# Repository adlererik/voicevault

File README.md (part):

# VoiceVault

**A dedicated encrypted voice device, being developed and tested in software before hardware is built.**

A phone can be an excellent communications modem and an unsafe place to handle a private conversation. VoiceVault explores a different boundary: put the microphone path, audio codec, encryption keys, verified contacts and call approval inside a separate device. Give the phone encrypted media to forward.

The intended adversary has **NSA-class capabilities**: both phones may already be completely compromised through Pegasus-like spyware, zero-day or zero-click exploits, and telecommunications and relays may be controlled by the attacker. **Supply-chain attacks are excluded from the current threat model.** The project starts after phone compromise; it does not attempt to prevent or reproduce the exploit that compromised the phone.

**Today:** working Rust voice simulations, hostile-phone processes, lifecycle security models, a live device-and-test dashboard and a linked Cortex-M33 diagnostic. **Destination:** a small independent voice endpoint with its own trusted display, wired headset audio, replaceable battery, wired charging and a carefully isolated BLE connection to a phone. No physical VoiceVault device has been built.

[Project vision](docs/PROJECT_VISION.md) · [Architecture](docs/ARCHITECTURE.md) · [Threat model](docs/THREAT_MODEL.md) · [Every security control](docs/SECURITY_CONTROLS.md) · [Why these algorithms](docs/CRYPTOGRAPHY.md) · [Test evidence](docs/RESULTS.md) · [Hardware roadmap](docs/ROADMAP.md) · [Hybrid call security](docs/POST_QUANTUM.md)

## Start here: using the two labs

**[Read the beginner's guide to `lab` and `firmware-lab`](docs/LABS_GUIDE.md)** for step-by-step instructions, screen controls, listening, test results, saved files and troubleshooting.

| I want to… | Use |
|---|---|
| Watch software voice calls through hostile phone processes | `./lab demo --seconds 30` at <http://127.0.0.1:8765/> |
| Run the full eleven-group native verification suite | `./lab watch` |
| Use the ARM device screen on the configured local workstation | `./firmware-lab device` at <http://127.0.0.1:8765/firmware> |
| Understand every option before starting anything | `./lab --help`, or local `./firmware-lab --help`; add `COMMAND --help` for details |

The labs reuse trusted Rust building blocks and test different surroundings. They have separate verdicts; neither automatically qualifies the other or a physical board. **The firmware runtime is currently local development work, not a runnable package in this GitHub checkout.** The guide explains that availability boundary and its public-test-key, timing and hardware limits.

[Native command reference](docs/CLI_REFERENCE.md) · [Local firmware command reference](hardware/firmware-lab/CLI.md) · [Native tool setup](docs/DEVELOPMENT.md)

## Hardware laboratory

**The [VoiceVault C1 LQFP144 layout](hardware/rev-c1/README.md) reached 98% routing.** Quilter finished six candidates at **21:19 CET on 16 November**. Independent KiCad review of candidate 3.1 confirms **six unfinished connections, zero copper shorts and zero schematic mismatches**. Hole-clearance, antenna and placement findings remain; no board is accepted for manufacture. [Actual returned PCB views and native findings](hardware/evidence/2026-11-17/c1-return-review/README.md). The owner subsequently authorized local KiCad repairs in a [separate checkpoint](hardware/rev-c1/local-repair-01/README.md). The uploaded input and raw cloud result remain preserved; [repair evidence](hardware/evidence/2026-11-17/c1-local-repair/README.md) tracks the additional wiring required by power-layout corrections.

The [latest checked local repair](hardware/rev-c1/local-repair-03/README.md) has 17 remaining native opens, zero KiCad rule violations and zero schematic mismatches. All three converter inductors are on their controllers’ faces; their switching connections have no vias, including the 2.924 mm MCU connection. Routing is still in progress. [Front and back CAD renders](hardware/visuals/2026-11-17/README.md) use the actual layout with some approximate component bodies.

C1 uses **STM32U5G9ZJT6Q LQFP144**, retaining the STM32U5G9ZJ platform while moving the MCU connections to accessible perimeter leads. The [package evaluation](hardware/rev-c/LQFP_EVALUATION.md) led to a complete 144-pin remap, a corrected hardware microSD clock on **PB13**, and three additional supply bypass capacitors. It retains **one NXP SE050E2 secure element, QFN nRF52832 BLE, a replaceable protected BL-5C-style lithium-ion pack interface, wired charging, trusted display/touch, wired audio, physical mic disconnect, offline microSD and separate development debug connectors**. Qi, NFC and vibration remain removed.

There are **199 electrical components—97 fewer than B0—plus 13 probes and four mounting holes: 216 footprints**. The provisional rectangle remains 70 × 45 mm, with a six-layer stack and ordinary vias. Populated-board fit, final routing and hardware qualification remain unverified.

**Checked input:** KiCad 10.0.8 reports **zero ERC violations and zero schematic-to-PCB mismatches**. All 144 MCU pins, 55 signal functions, 711 functional pin-net assignments and 72 retained critical circuit checks pass. Seven corrupted-pin controls and five isolated RF rule controls pass. The empty input has **587 connections to route**; that is intentionally a fresh layout, not a repaired-board result. All 18 server input files exactly match the checked source, and downloaded cloud settings match 76 reviewed bypass entries, 14 current budgets, three converter loops, four crystals and 21 proximity requirements. [Actual checks, hashes and limits](hardware/evidence/2026-11-16/c1-preparation/README.md).

*Native KiCad view of candidate 3.1, showing the central LQFP144 MCU. This reviewed cloud return has remaining failures and has not replaced the live board.*

**ngspice 47** completed 27 revised passive MCU core-output sensitivity cases. The model has no MCU regulator control loop and does not qualify stability or hardware behavior. Earlier unchanged C0 subcircuit studies include 772 passive audio/backlight cases, 16 secure-bus RC cases and a supplier radio-switch model; the main buck-boost supplier model remains numerically blocked. [C1 evidence](hardware/evidence/2026-11-16/c1-preparation/README.md) · [Earlier subcircuit reports and plot](hardware/evidence/2026-11-16/quilter-launch/README.md).

**Manufacturing remains blocked.** Final routing/connectivity, native DRC, RF/power/audio/mechanical review, battery/holder and assembly sourcing, production firmware and real hardware security tests remain open. No board has been ordered or built, and no purchase or paid service was used.

The [original BGA C0 revision](hardware/rev-c/README.md), rejected [95% Quilter return](hardware/evidence/2026-11-16/quilter-retry-01-return/README.md), [isolated 62-open repair](hardware/rev-c/local-repair-01/README.md), live B0 and all earlier FreeRouting/cloud evidence remain preserved. [Historical hardware laboratory and tool/MCP details](hardware/README.md).

## The idea: move the endpoint

An ordinary encrypted calling app processes plaintext on the phone. Once an attacker controls that operating system, network encryption alone cannot protect audio the operating system can already access.

VoiceVault's intended device owns the sensitive endpoint. Contacts are verified there, calls are approved there, and audio is encoded and encrypted there before reaching the phone. The phone carries encrypted records and necessary signaling; it does not become a trusted authority for identities, consent, keys, time, entropy or firmware.

This distinction depends on the physical audio path. The proposed host-phone arrangement includes removing its microphones and speakers, keeping voice on an external wired headset connected to VoiceVault, and validating remaining acoustic pickup paths. An unmodified compromised phone nearby can still record speech through its own microphone. [Why a separate device, and its limits](docs/DEVICE_RATIONALE.md)

*Architecture illustration. Analog audio and BLE are hardware targets; current calls use synthetic audio and bounded local IPC. Public signaling and transport metadata remain observable.*

## A real software foundation

The lab makes two endpoints conduct a simultaneous encrypted voice exchange through two hostile phone processes and a relay. It uses actual Opus and actual cryptography, produces recovered WAV files, injects delivery faults, and records results for inspection.

| Built and exercised | What it establishes |
|---|---|
| Two voice endpoints and three hostile transport processes | A concrete separation between trusted audio/key handling and untrusted delivery, under a trusted Linux host |
| Confirmed enrollment, pinned contacts and signed invitations | Explicit identity, consent, replay and accepted-call binding rules |
| Real Opus → Noise encryption → hostile transport → authentication → decode | An executable media pipeline, including loss and malformed-input handling |
| Stored-contact, entropy, radio and offline-update models | Testable device-local policy before selecting physical chips |
| The same trusted crates compiled without `std` and linked for Cortex-M33 | Functional CPU execution and measured memory fit under a named capacity budget |
| An event-backed dashboard with searchable individual results | Visible checks, named test outcomes, attack traces and saved replays |

A tested model is not a finished hardware protection. The [assurance case](docs/ASSURANCE.md) states which assumptions each result depends on.

## The threat model and the protections

The attacker may observe, drop, replay, modify, reorder, delay and inject traffic; collude across both phones and relays; impersonate contacts; flood ingress; and try to turn malformed messages into unauthorized device actions. The design also tests a malicious authenticated peer, because having a valid key does not make compressed audio harmless.

| Attack or failure | Protection in the software model | Boundary |
|---|---|---|
| Intercept or modify voice | ChaCha20-Poly1305 under authenticated Noise transport keys | Trusted endpoints and sound implementations are assumed |
| Substitute a peer during enrollment | Noise XX, signed identity/DH records, full transcript comparison and confirmation on both sides | Trusted local comparison is required; hardware UI is future work |
| Spoof a contact or call invitation | Pinned Ed25519 identity, recipient binding, boot challenge, expiry and persisted counters | Invitation metadata itself is not confidential |
| Reuse a different invitation for an authenticated call | The hybrid Noise prologue binds the signed offer and acceptance and both verified identities | Local approval remains separate from remote signaling |
| Save encrypted calls for future quantum decryption | Fresh X25519 and ML-KEM-768 establish each call, with the hybrid suite required | Depends on the hybrid construction, trusted endpoints and erasure |
| Replay media or poison the replay window | Monotonic sending, directional keys, authenticated counter/slot checks and a bounded replay bitmap | Invalid input cannot commit incoming replay state |
| Activate audio through the phone | Local consent plus encrypted Confirm/Ready; no radio mic/consent opcode | Actual headset and physical disconnect still need validation |
| Infer speech or silence from record length | CBR Opus, DTX off, fixed 128-byte records and encrypted filler | Call boundaries, timing errors, location and correlation remain visible |
| Exhaust queues or force a burst after a stall | Bounded ingress, assembly and jitter queues; expiry; absolute deadlines; missed slots discarded | A hostile network can still deny service |
| Roll back stored contacts or signaling counters | Owner-bound AEAD snapshots tied to a protected monotonic generation | Protected storage is modeled, not a chip driver |
| Push firmware through the phone | No remote updater; locally authorized signed-image policy | Physical boot/update enforcement remains future hardware work |
| Install an old, corrupt or wrong-device image | Target/version/hash/signature checks, protected floor, two banks and readback | Real flash and counter atomicity are unmeasured |
| Interrupt an offline update | Preserve the active bank, write header last, verify before boot/version handoff | Tests cover modeled write cuts and selected torn writes |
| Weaken randomness through the phone | Onboard-only entropy-source interface, failure checks and two-source policy | Hardware entropy quality and independence need measurement |
| Keep using a closed or expired session | Irreversible close, owned key destruction, bounded media epoch and fresh handshake | Complete erasure and seamless renewal remain open |

The [complete control register](docs/SECURITY_CONTROLS.md) links each protection to its code, evidence, assumptions and remaining hardware work.

## Why these cryptographic choices?

| Choice | Role and reason |
|---|---|
| **X25519** | Compact Diffie–Hellman key exchange with fresh per-call ephemeral secrets; separate from signing identities |
| **ML-KEM-768** | Adds a fresh post-quantum secret for each call using the portable `libcrux-ml-kem` implementation |
| **Ed25519** | Signed identities, contact bindings, invitations and offline-image authorization |
| **ChaCha20-Poly1305** | Established authenticated encryption for voice and stored snapshots; suitable for portable software implementations |
| **BLAKE2s** | A 32-bit-oriented hash for the selected Noise suite, domain-separated bindings and firmware digests |
| **Noise's HMAC/HKDF-BLAKE2s** | An established transcript-bound key schedule and separate transport keys for each direction |
| **Noise XX / KKhfs through Snow** | XX for first enrollment and the experimental hybrid KK modifier for calls between pinned contacts |
| **Opus** | Practical speech compression; hard CBR and no DTX work with the outer fixed-size envelope |
| **Rust with `no_std` integration** | Safe parsing/state code and bounded interfaces that can migrate toward embedded firmware |

The hybrid suite is required for new calls. Both peers authenticate the full exchange and its algorithm suite before local consent and encrypted confirmation open audio. ML-KEM-768 is an explicit exception to the owner’s preference to avoid NIST algorithms where practical. [Protocol and wire format](docs/POST_QUANTUM.md) · [Cryptographic rationale](docs/CRYPTOGRAPHY.md)

## Evidence you can inspect

The hybrid v2 run on **2026-11-11** passed **all 11 required groups and 48 checks**. The suite recorded 68 named outcomes, including five bounded Kani checks, and ran eight fuzz campaigns for at least 120 seconds each. It also checked 80 ML-KEM-768 vectors. The altered-startup scenario verifies that a compromised phone cannot open either audio path by modifying the key exchange.

| Recorded result | Observation |
|---|---|
| Real encrypted audio | Both directions recovered generated audio through two hostile phone processes and a relay |
| Cortex-M33 execution | Hybrid startup, fragmentation and 32 Opus frames executed in QEMU |
| Linked image and observed stack | 863,104 bytes of a 983,040-byte slot and 84,876 bytes of a 131,072-byte stack reserve |
| Reference memory budget | 37,500 bytes unassigned after static state and stack/display/driver reservations |

[Latest raw results](docs/evidence/hybrid-v2/) · [What each fuzz target tests](docs/FUZZING.md) · [All recorded runs](docs/RESULTS.md) · [Embedded fit](docs/PLATFORM.md)

*Actual dashboard capture during hybrid handshake fuzzing. The device panels show the earlier live call in the same run. [Live call capture](docs/screenshots/command-deck-live-laptop.png) · [Historical full-suite completion](docs/screenshots/voicevault-complete.png)*

## See what is happening as it happens

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
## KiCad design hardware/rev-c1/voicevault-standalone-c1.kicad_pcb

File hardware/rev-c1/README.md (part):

# VoiceVault C1 — LQFP144 prototype

**Local repair is now authorized and in progress.** See the [latest checked repair: 17 opens, zero native violations](local-repair-03/README.md), the [preserved earlier repair](local-repair-01/README.md) and [native repair evidence](../evidence/2026-11-17/c1-local-repair/README.md). The six-open count below describes the untouched cloud return. Moving power parts and removing invalid copper required additional connections to be rebuilt in the repair copy.

**Quilter finished at 21:19 CET on 16 November 2026: six candidates, all reporting 98% routing. Not for fabrication.** Independent KiCad review of candidate 3.1 confirms **six missing connections, zero copper shorts and zero schematic-parity mismatches**, but hole-clearance and antenna-rule failures remain. [Actual returned board views, exact findings and next work](../evidence/2026-11-17/c1-return-review/README.md). The owner approved **STM32U5G9ZJT6Q** on 16 November 2026. C1 is a separate revision; all earlier revisions and results remain preserved.

[Open the completed C1 job](https://app.quilter.ai/jobs/6afb49addfae511781423d99?candidate=3) · [Recorded launch and settings](../evidence/2026-11-16/c1-preparation/launch.json). Candidate 3.1 was downloaded and reviewed in separate work folders; it has not replaced the checked input or live board and is not accepted for release.

[KiCad project](voicevault-standalone-c1.kicad_pro) · [Root schematic](voicevault-standalone-c1.kicad_sch) · [Clean PCB input](voicevault-standalone-c1.kicad_pcb) · [Review inventory](BOM-REVIEW.csv) · [Exact circuit target](board-target.json) · [Checked evidence](../evidence/2026-11-16/c1-preparation/README.md) · [Package evaluation](../rev-c/LQFP_EVALUATION.md)

## Implemented circuit changes

| Area | C1 change |
|---|---|
| MCU | STM32U5G9ZJT6Q, LQFP144, 20 × 20 mm body, 0.50 mm pitch; native symbol and 144-pad footprint |
| Pin mapping | All 144 physical pins checked against pinned ST data, including all 55 connected signal functions and 91 connected supply/reference/signal pins |
| microSD | Move SD_SCK_MCU from PC0, which lacks SPI2_SCK, to unused PB13 / pin 70; retain PC1 MOSI, PC2 MISO and PC7 software chip select |
| Supplies | Map every LQFP supply/ground pin explicitly; retain both VDD11 pins and connect **both** VDD11DSI pins to MCU_VDD11 |
| New bypass parts | C113 at VDD pin 122, C114 at VDD pin 144, C115 at VDD11DSI pin 20; each 100 nF / 10 V |
| Debug | Retain STDC14 SWD/SWO/UART and reset on package-correct pins; development access remains open |
| CAD consistency | Preserve explicit single-pad no-connect net names for native parity. JP501 is a copper solder bridge excluded from purchasing BOM, with matching symbol/footprint attributes |
| Cloud settings | Replace all old MCU ball identifiers with LQFP pin numbers; 76 actual rail/reference bypass definitions. Exclude 12 oscillator, RF, reset, audio-filter and timing capacitors from the supply-bypass list |

Inventory is **199 electrical footprints, 13 probes and four mounting holes: 216 total**, versus C0's 213. The only changed existing component value is U1's order code. Every existing functional non-MCU connection and all four mounting-hole positions are preserved. New MCU wiring is a package remap plus the explicit SD-clock correction. [Delta checks](../evidence/2026-11-16/c1-preparation/circuit-delta.json).

The one SE050E2, larger QFN nRF52832, BQ24074 wired charger, replaceable protected lithium pack interface, audio codec/headset/mic disconnect, display/touch, microSD and local controls remain. Qi, NFC and haptics remain removed. Battery/holder/display assembly acceptance, charging safety and production-ready component sourcing remain open; this inventory is not an assembler-approved order file.

## Power-pin allocation

| LQFP supply | Pins | Local 100 nF assignments |
|---|---|---|
| VDD | 25, 41, 55, 69, 83, 89, 95, 109, 122, 144 | C7, C12, C17, C14, C10, C11, C9, C16, C113, C114 |
| VDDDSI | 13 | C8; C110 provides the existing additional bulk bypass |
| VDD11DSI | 14, 20 | C23, C115; connect to MCU_VDD11, never directly to 3.3 V |
| VDD11 | 67, 142 | C22, C24; C107/C27 retain the two 2.2 µF core capacitors |
| VDDSMPS | 65 | C26; C25/C108 retain existing input bulk capacitance |
| Other domains | VBAT 6, VREF+ 34, VDDA 35, VDDUSB 108, VDDIO2 131 | Existing domain-specific caps remapped and checked |

L1 remains between VLXSMPS pin 64 and MCU_VDD11. VSSSMPS pin 66 is ground. Correct values and pin associations are necessary; actual close placement, short switching loops, return paths, capacitor derating/ESR and measured regulation remain acceptance gates. The [full pin/net CSV](../evidence/2026-11-16/c1-preparation/mcu-pin-net.csv) includes unused and ground pins.

## Verification completed

Using KiCad **10.0.8**:

- Native ERC: **zero violations**.
- Native DRC of the off-board inventory: **zero layout violations**; explicit schematic-parity check: **zero mismatches**.
- Native netlist/PCB comparison: **711 functional pin-net assignments**, 826 exported nodes including explicit unused pins.
- All 144 MCU pin assignments, 55 signal functions and the retained 72 critical circuit/boundary checks pass. **Seven deliberately corrupted mappings are rejected**, including SD-clock, core/DSI power, debug, radio-to-secure-bus and C115 faults.
- **Five isolated native RF controls pass**: same-side feed allowed; opposite-side, inner-layer, wrong-net and out-of-corridor routes rejected. These fixtures do not route the real board.
- Full native ratsnest: **587 connections to route**. This is a new blank PCB, not the 62-open repaired BGA layout. There are **zero tracks, vias or copper pours**. All 212 non-mounting footprints are unlocked and parked outside the outline for Quilter to place.

With **ngspice 47**, 27 bounded passive core-output cases include the extra DSI bypass capacitor and sweep assumed inductance, bulk-cap derating and winding resistance. Observed idealized core extrema are **1.0148–1.1854 V**. The model has an ideal averaged source and **no MCU regulator control loop**: these are sensitivity results, not stability, power-integrity or hardware qualification. Six simulator-result checks ensure aborted/incomplete/non-finite outputs cannot be called successful. Unchanged C0 power/audio model limitations remain open.

Run `./hardware/check --rev-c1` for the native circuit/pin checks. [Evidence and additional test commands](../evidence/2026-11-16/c1-preparation/README.md).

## Placement and routing plan

Quilter performed the original full placement and routing. The original uploaded C1 input in this directory contains no FreeRouting copper, prior cloud copper or local electrical placement. The owner later authorized local repairs in the separate checkpoint linked above. The first outline remains a provisional **70 × 45 mm** rectangle. The 23.3 mm MCU courtyard bounding box fits the bare outline; populated-board fit must be established by placement and mechanical review. A larger serviceable rectangle remains an option if the actual layout requires it.

Use the standard JLCPCB **six-layer 4 mil preset**, S/GND/S/S/GND/S, **1.538 mm modeled thickness**, ordinary **0.45/0.20 mm vias**, and 0.50 mm board margin. This is a layout study against provisional published limits, not a manufacturing-stack approval or price quote. Two ground references are retained; a dedicated power plane is not required by this study. Real trace/pour current capacity and RF impedance still need review.

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
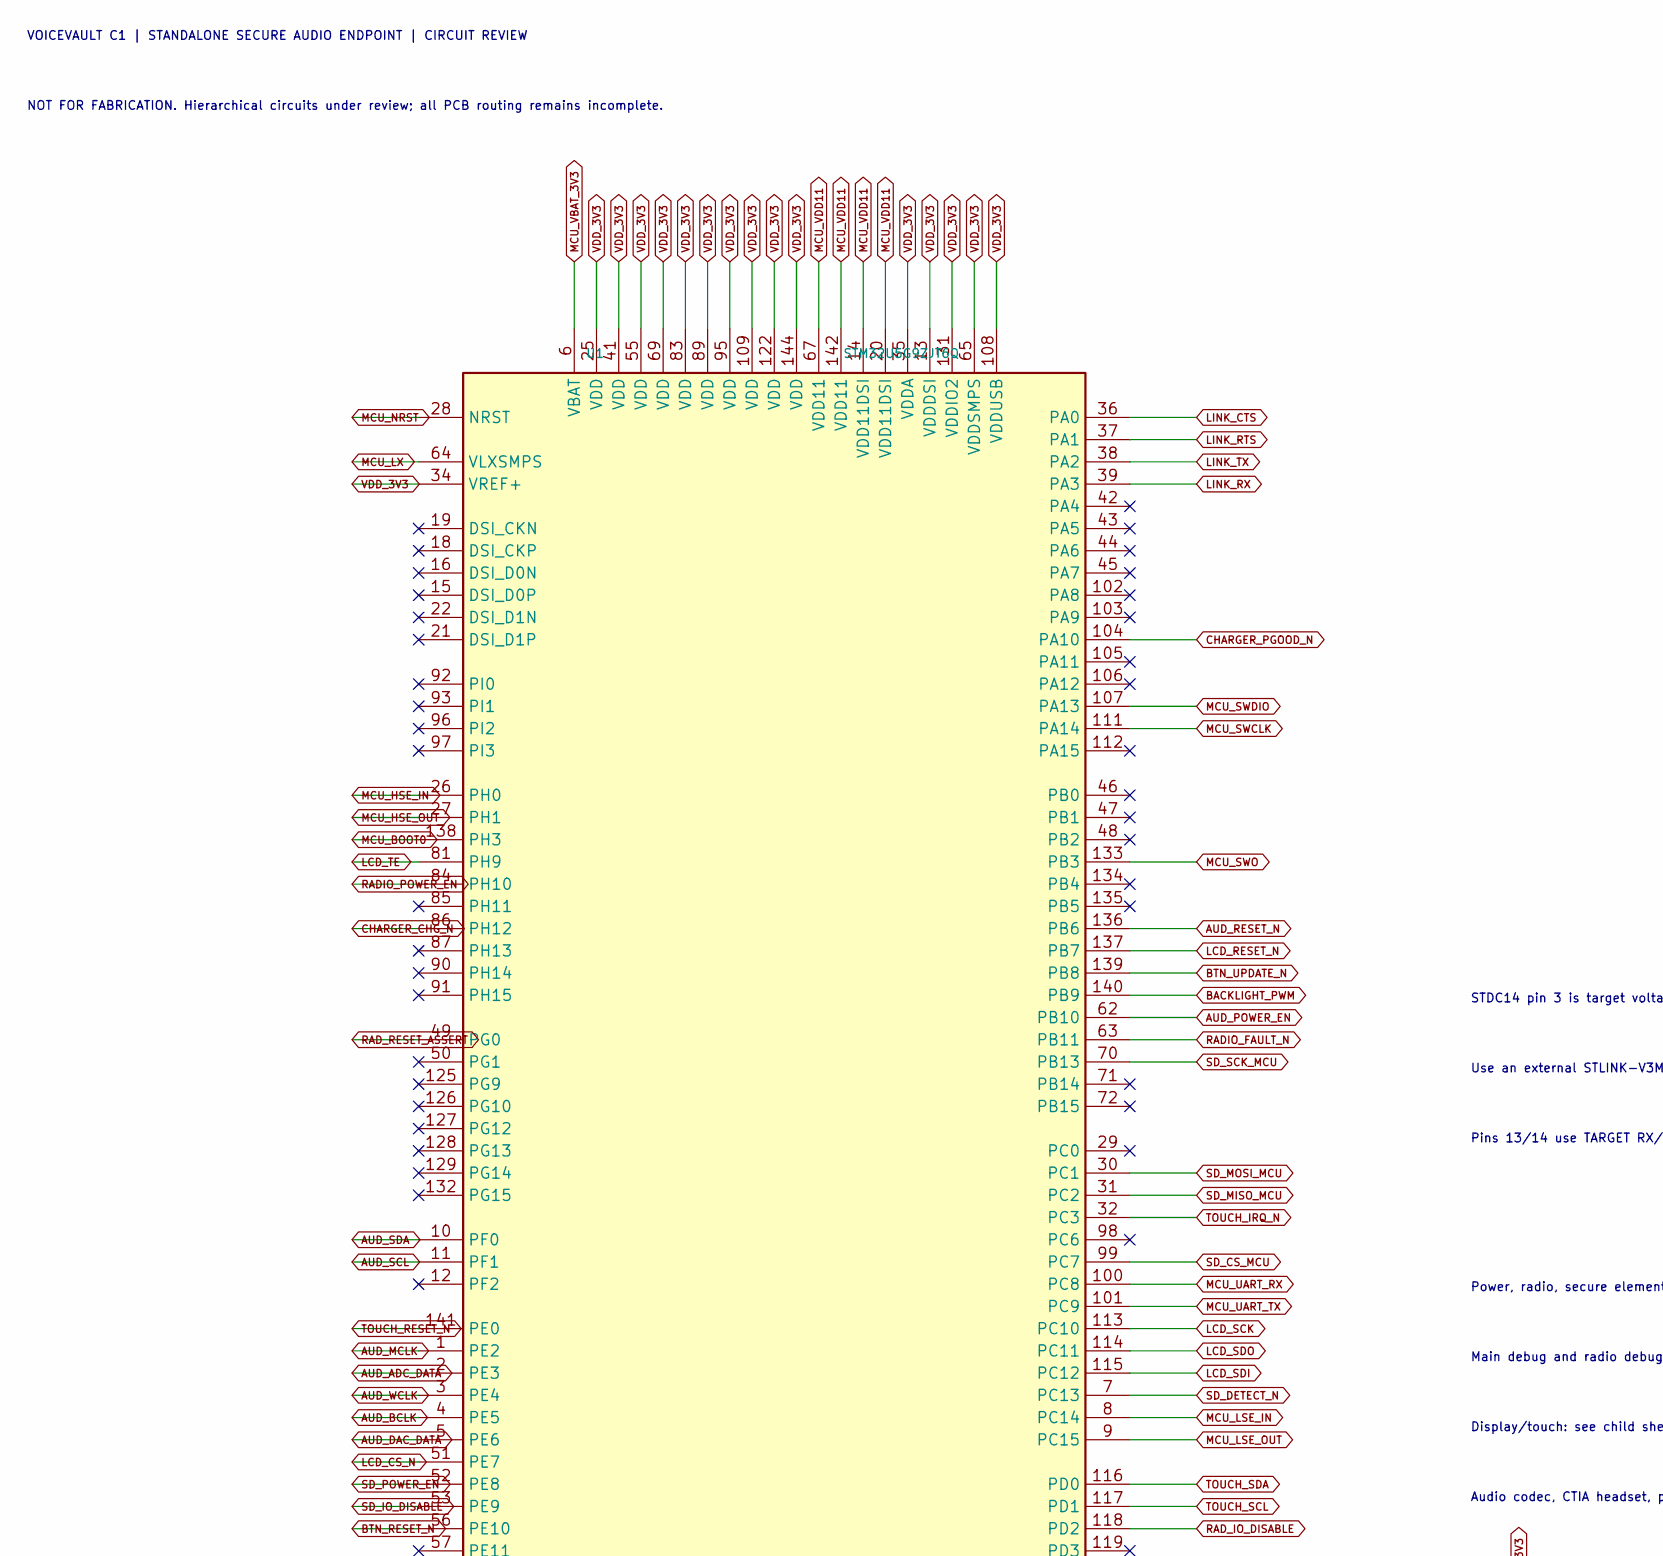
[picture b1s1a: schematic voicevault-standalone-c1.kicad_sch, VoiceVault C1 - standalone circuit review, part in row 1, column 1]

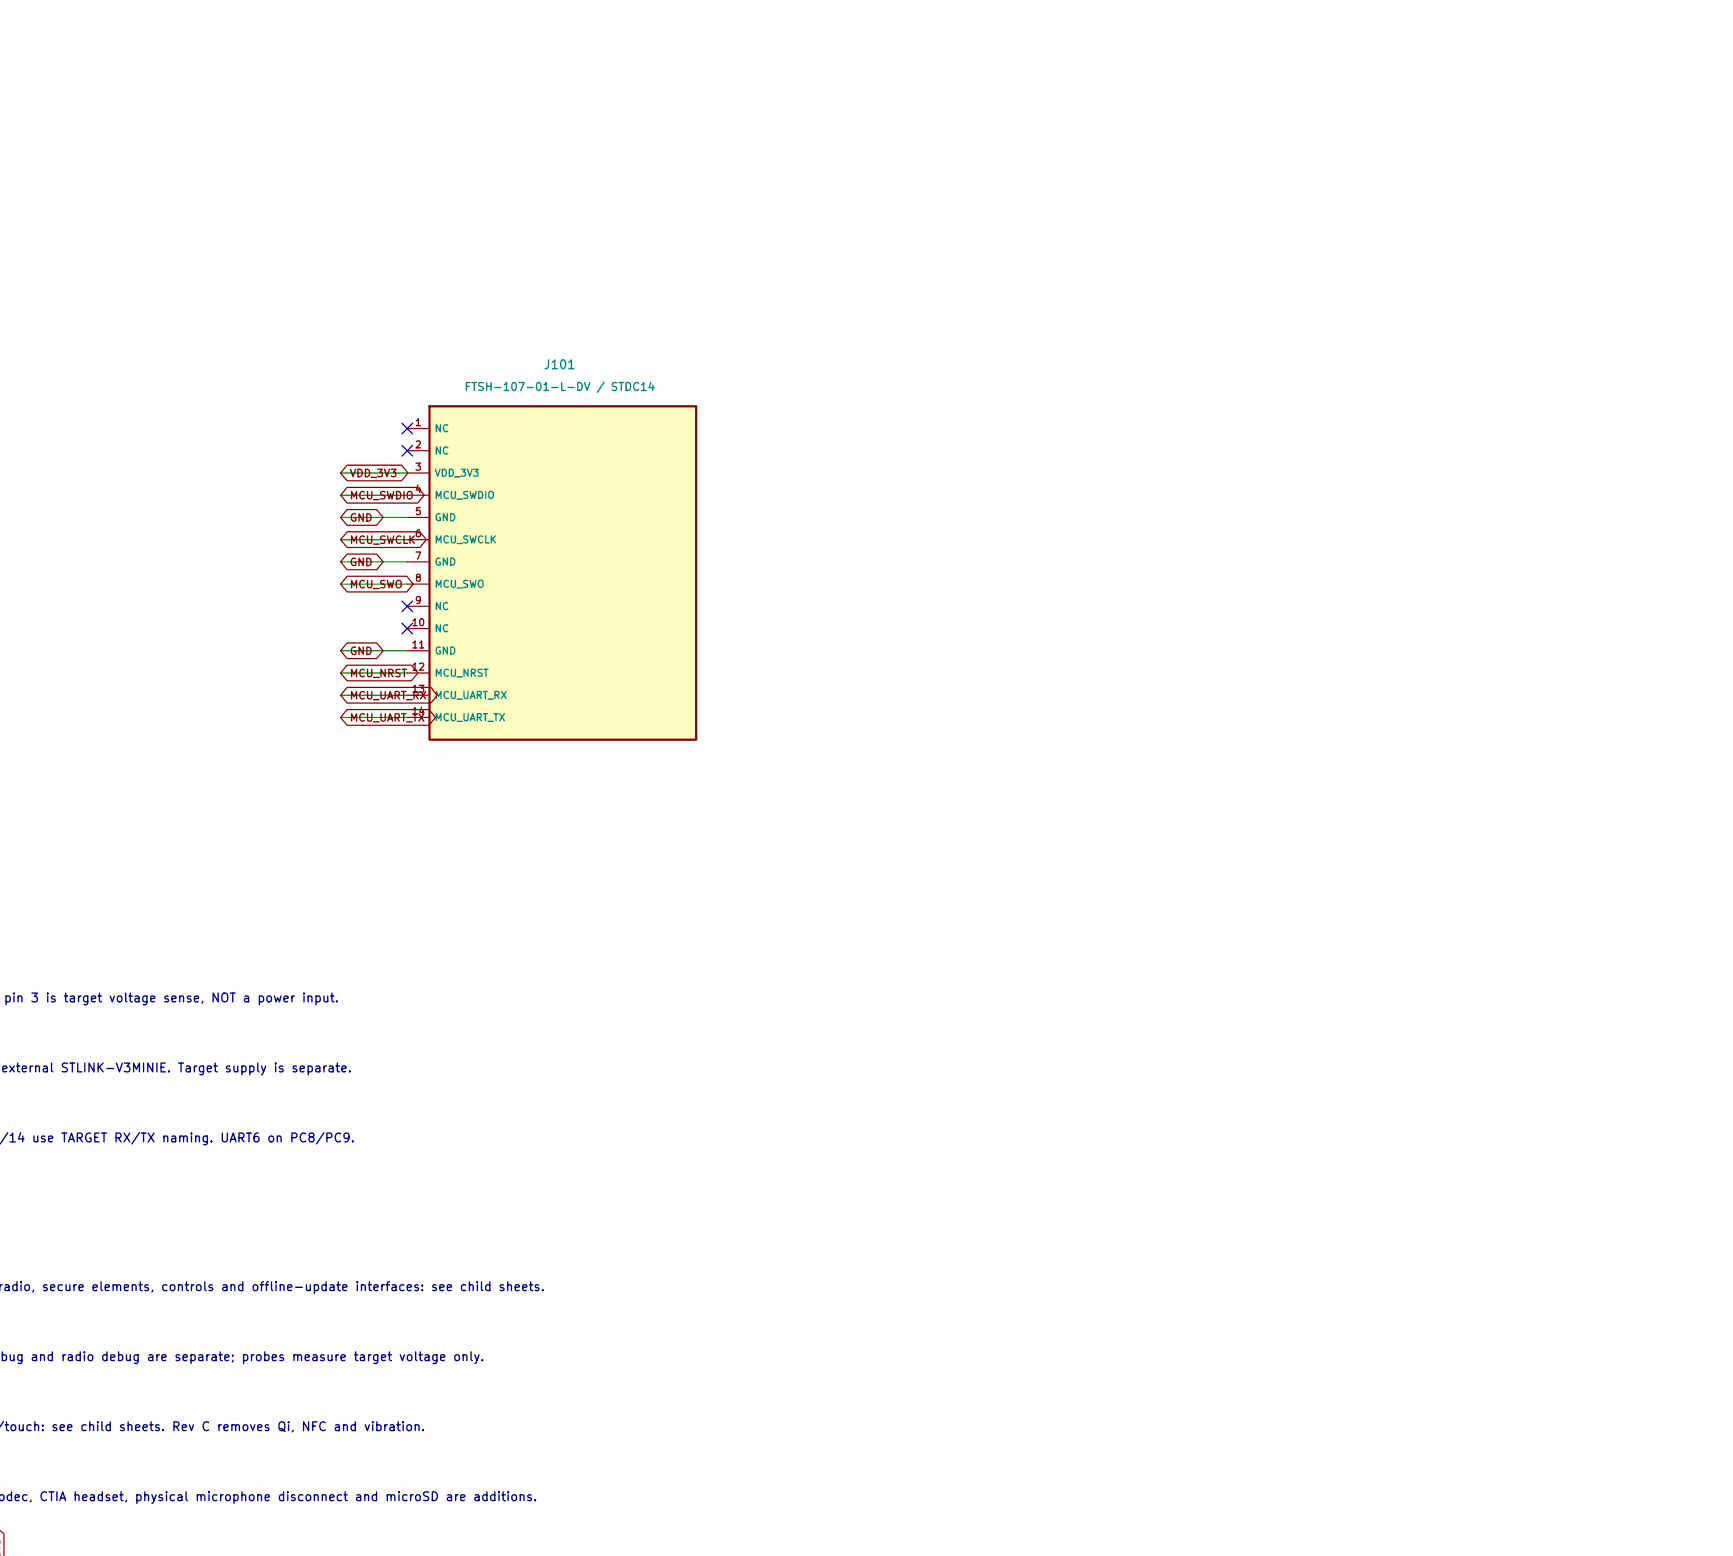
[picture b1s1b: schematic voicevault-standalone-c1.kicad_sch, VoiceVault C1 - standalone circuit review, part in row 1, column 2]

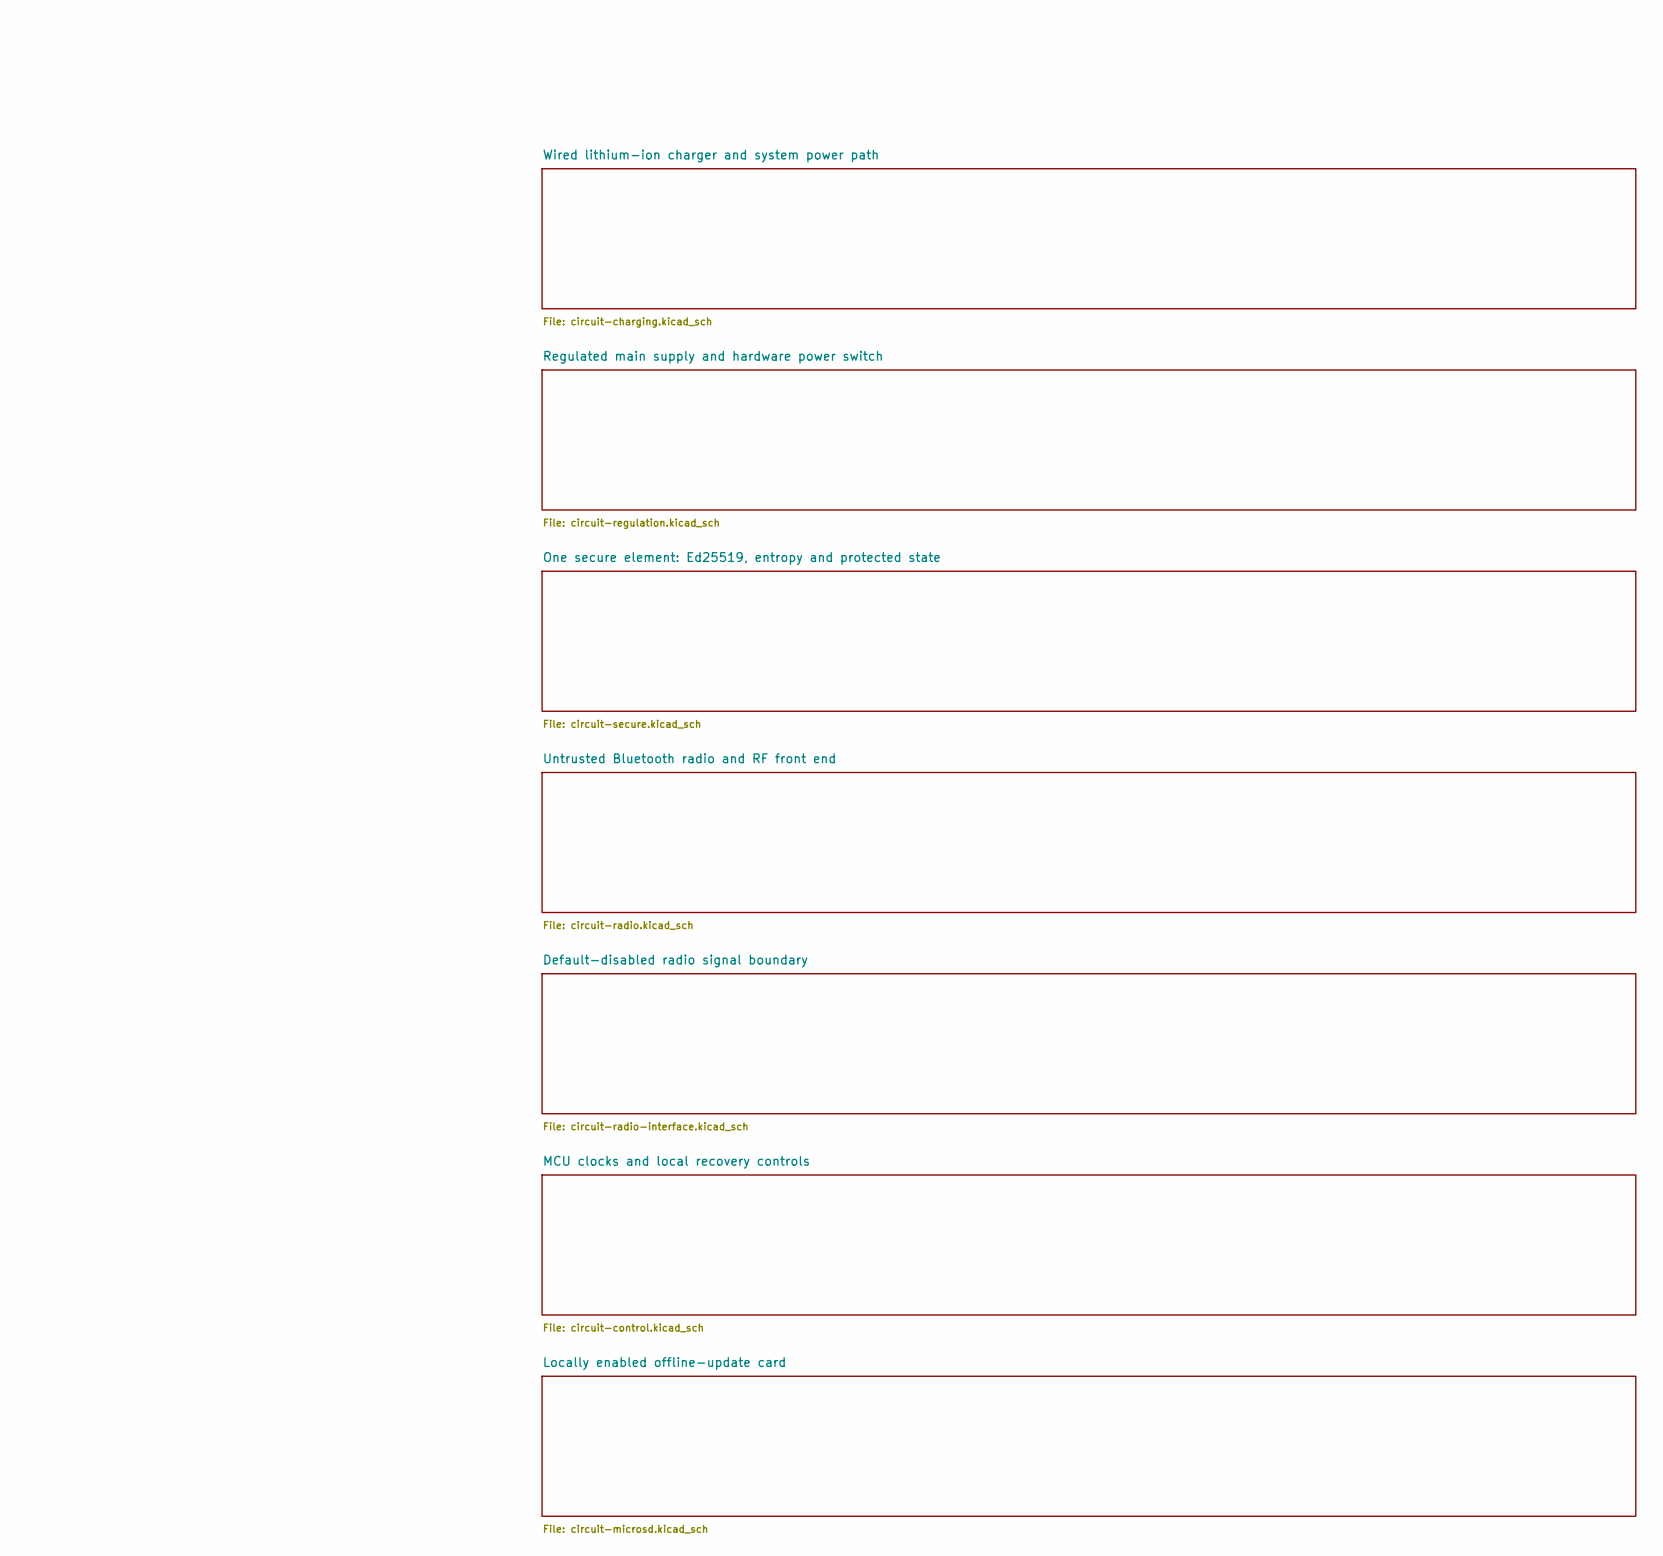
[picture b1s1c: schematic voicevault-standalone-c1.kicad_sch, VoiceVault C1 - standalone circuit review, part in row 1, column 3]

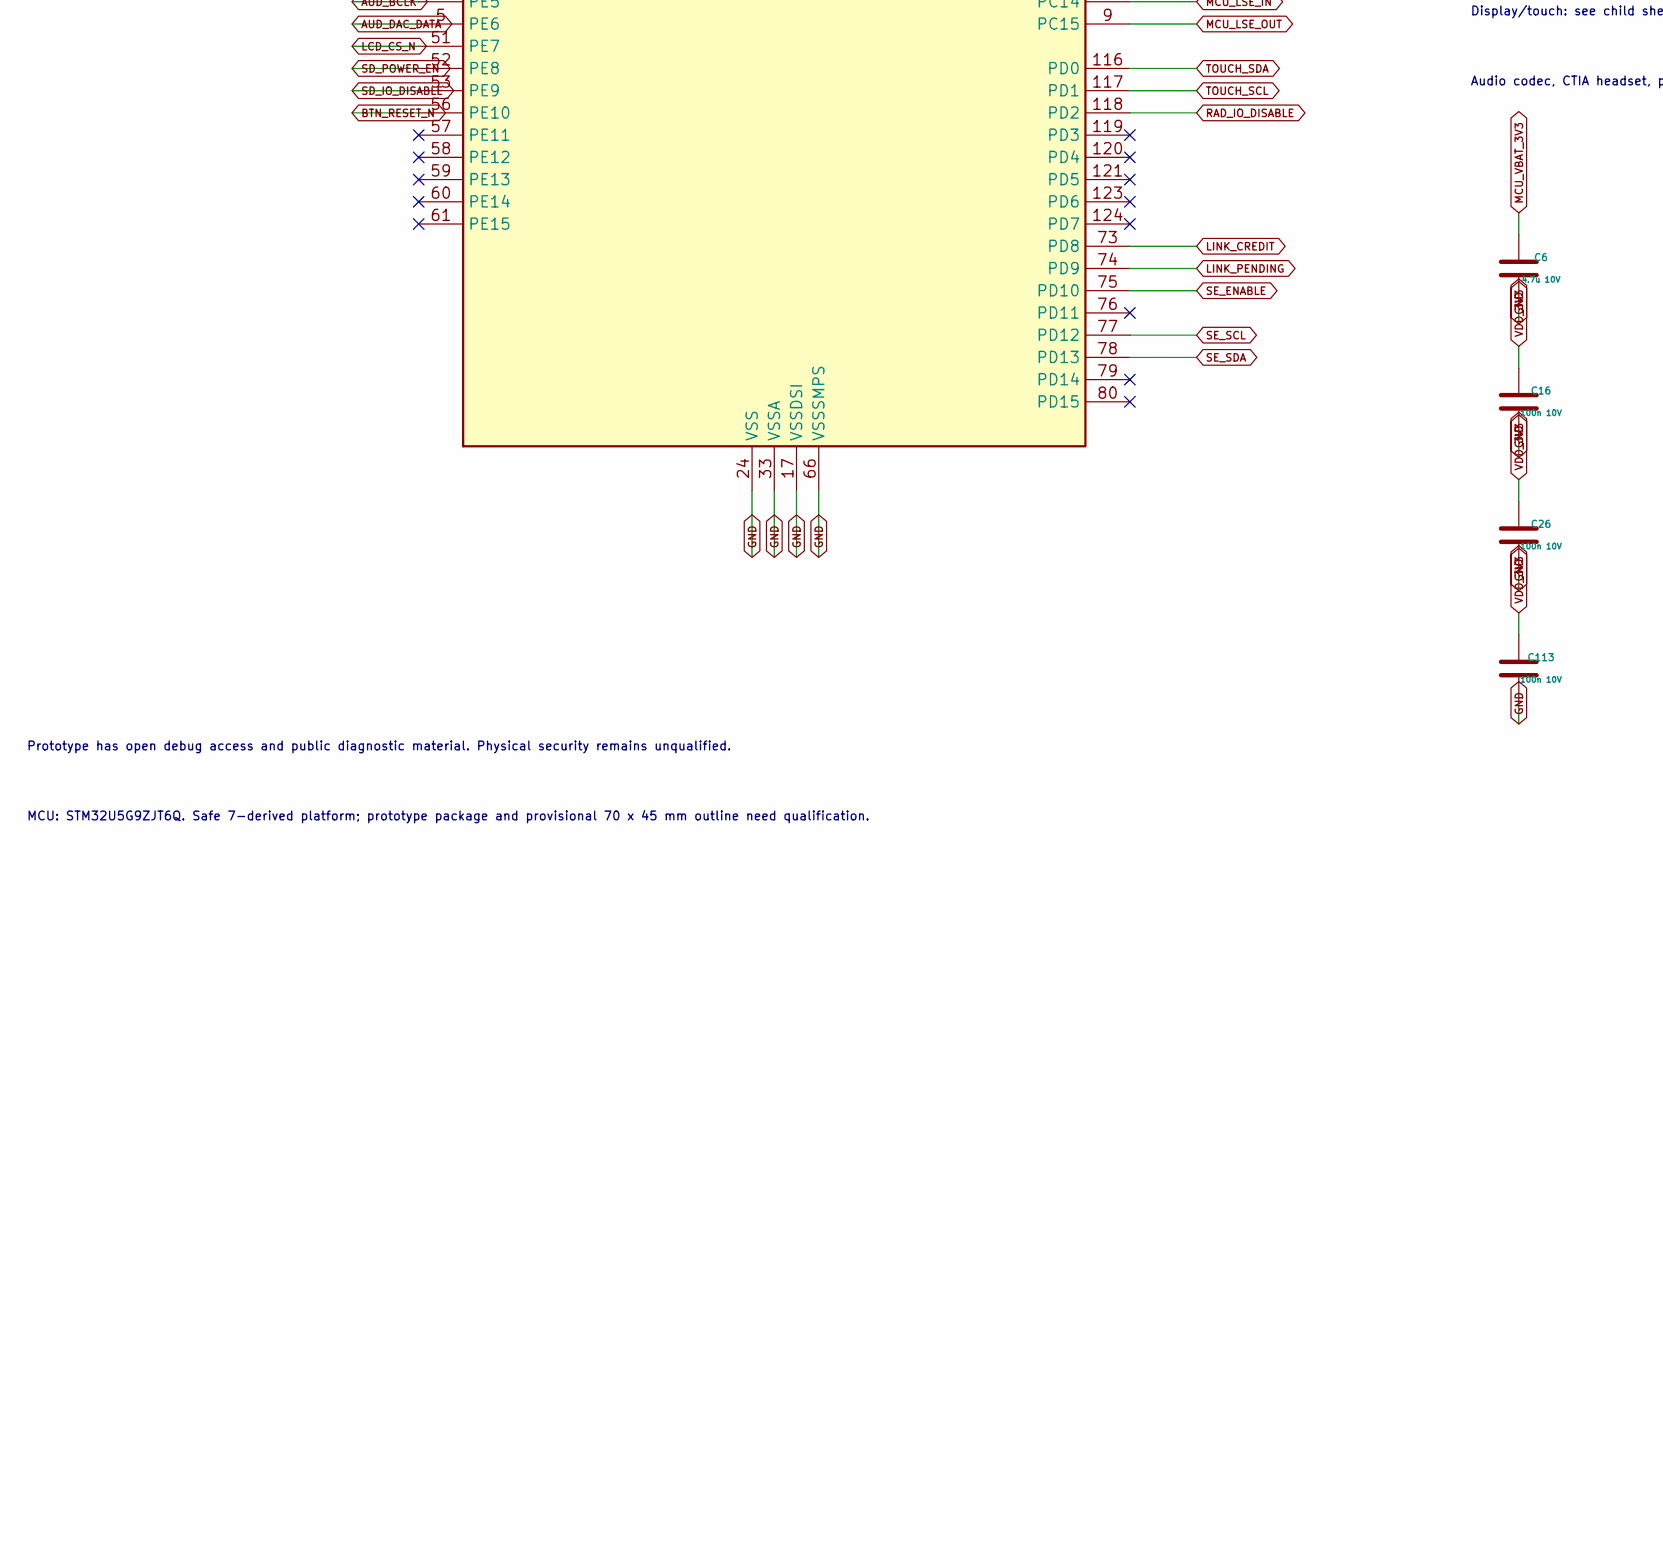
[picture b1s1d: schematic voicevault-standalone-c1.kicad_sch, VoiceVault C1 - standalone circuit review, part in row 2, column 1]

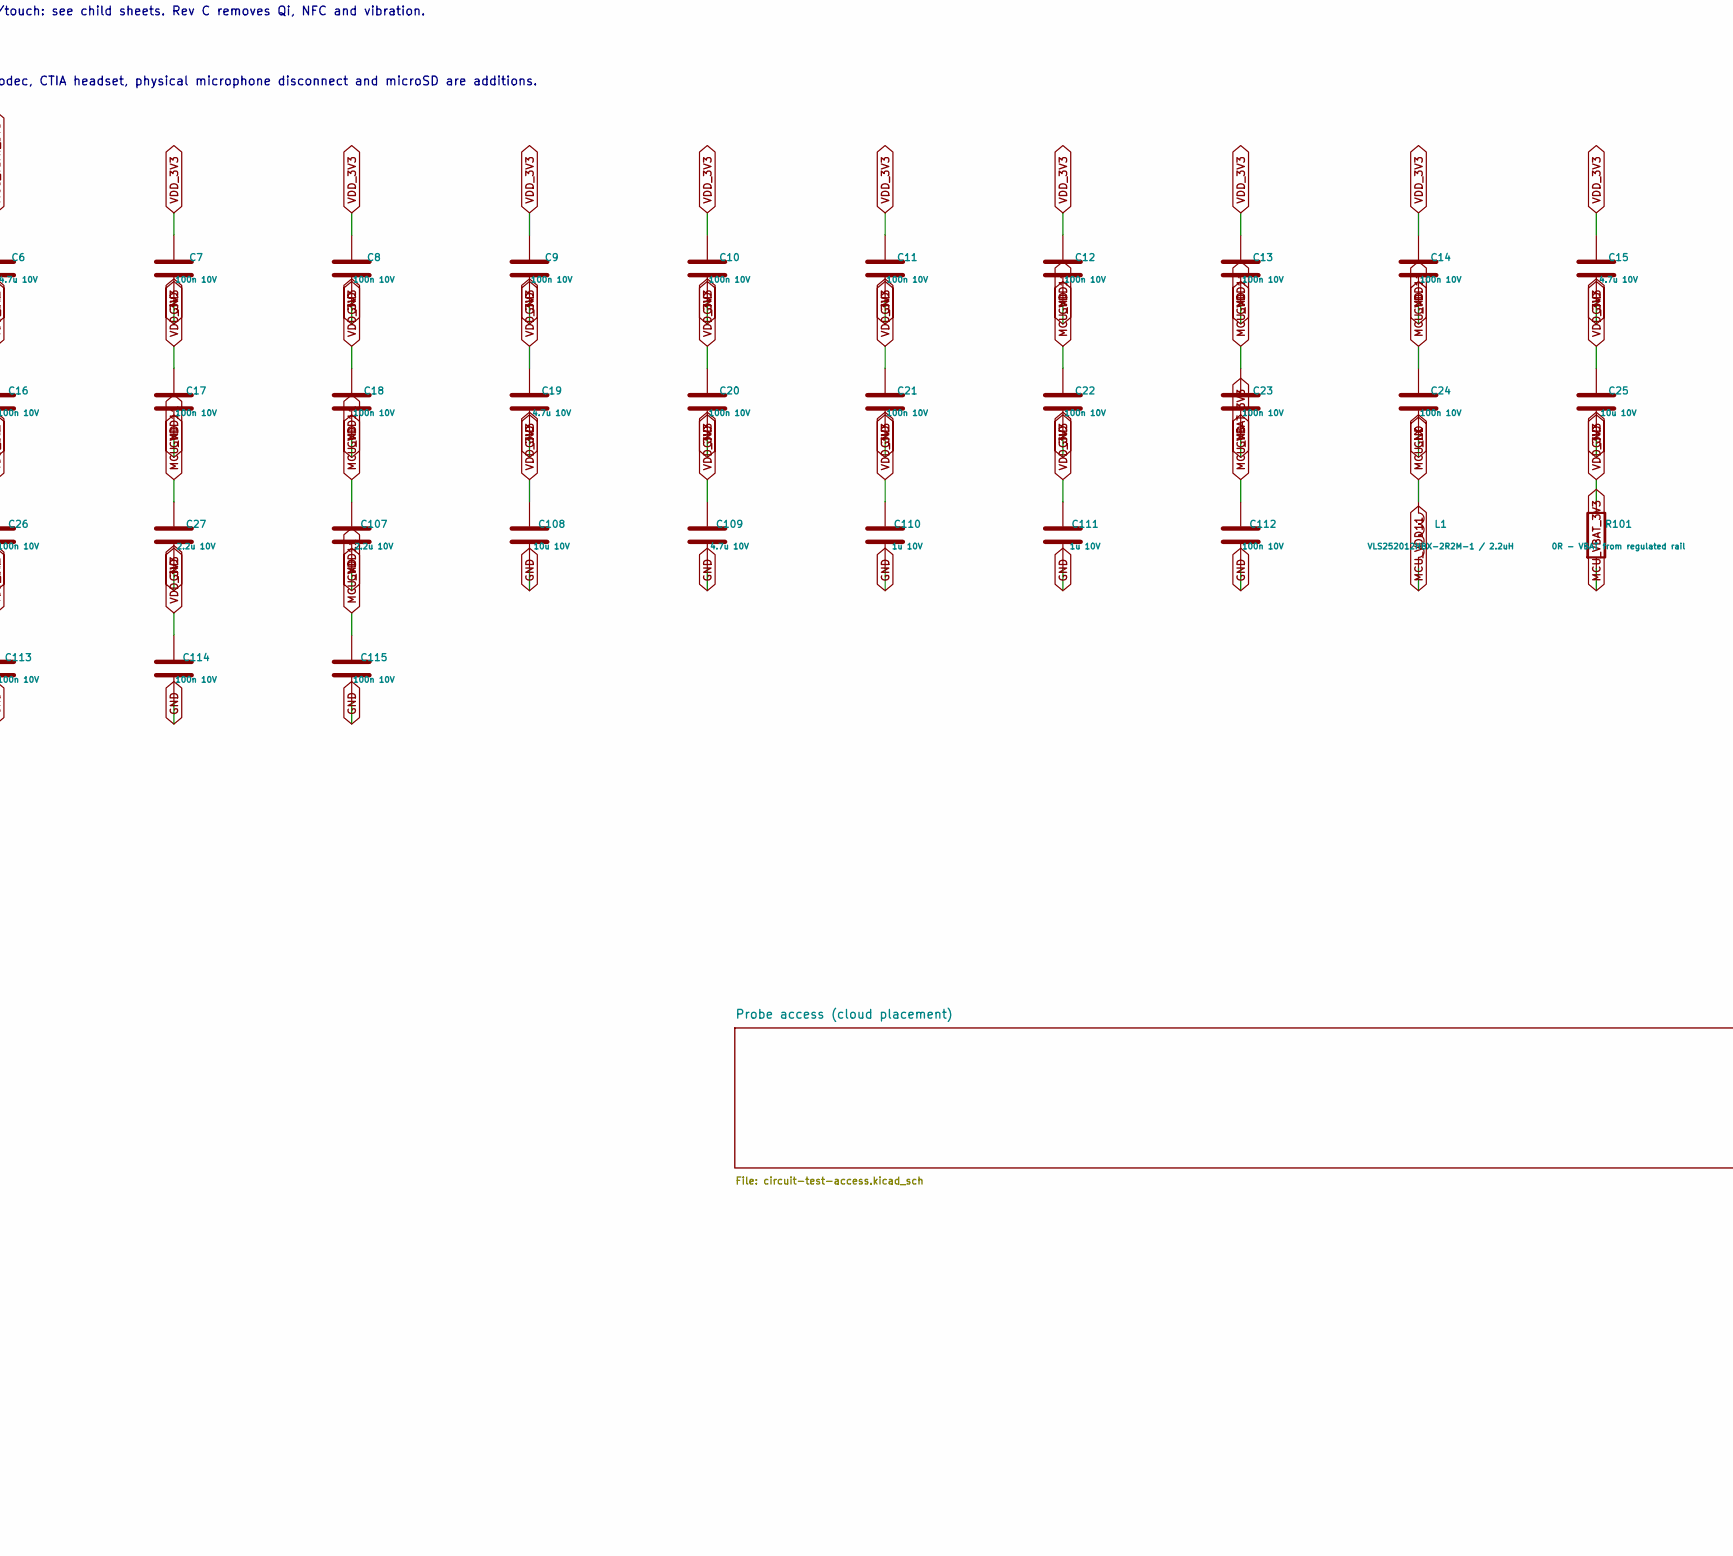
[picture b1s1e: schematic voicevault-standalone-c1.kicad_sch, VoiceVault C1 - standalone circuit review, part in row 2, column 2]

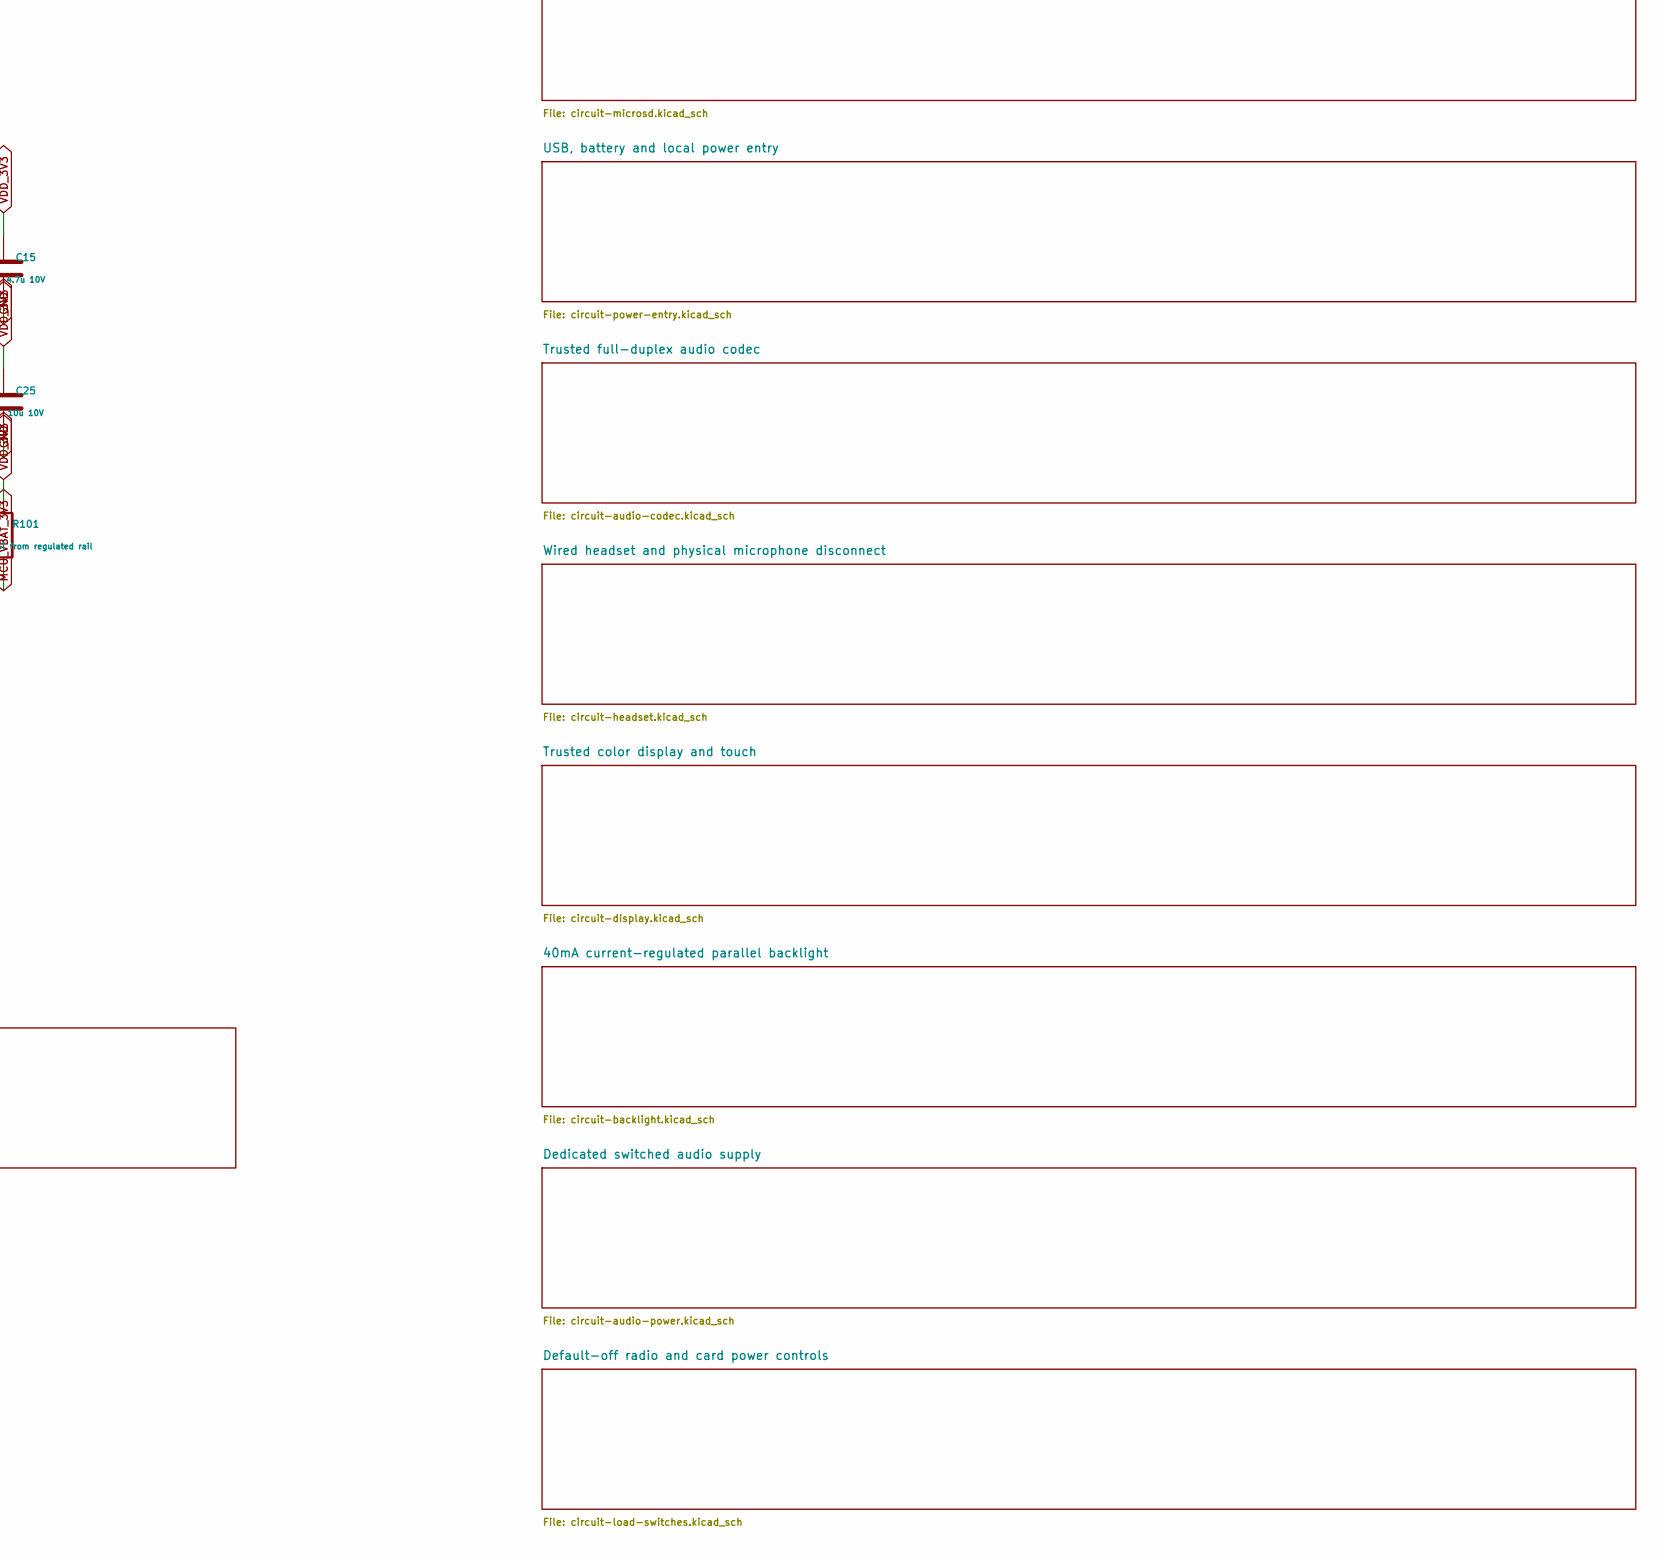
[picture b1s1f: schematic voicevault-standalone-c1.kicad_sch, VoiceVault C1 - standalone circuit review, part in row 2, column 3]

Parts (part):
C6, C15, C19, C109: 4.7u 10V; C_0603_1608Metric
C7, C8, C9, C10, C11, C12, C13, C14, C16, C17, C18, C20, C21, C22, C23, C24, C26, C112, C113, C114, C115: 100n 10V; C_0402_1005Metric
C25, C108: 10u 10V; C_0805_2012Metric
C27, C107: 2.2u 10V; C_0603_1608Metric
C110, C111: 1u 10V; C_0603_1608Metric
J101: FTSH-107-01-L-DV / STDC14; Samtec_FTSH-107-01-L-DV
L1: VLS252012HBX-2R2M-1 / 2.2uH; L_1008_2520Metric
R101: 0R - VBAT from regulated rail; R_0402_1005Metric
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
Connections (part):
AUD_ADC_DATA: U1.2 (PE3); also elsewhere on the board
AUD_BCLK: U1.4 (PE5); also elsewhere on the board
AUD_DAC_DATA: U1.5 (PE6); also elsewhere on the board
AUD_MCLK: U1.1 (PE2); also elsewhere on the board
AUD_POWER_EN: U1.62 (PB10); also elsewhere on the board
AUD_RESET_N: U1.136 (PB6); also elsewhere on the board
AUD_SCL: U1.11 (PF1); also elsewhere on the board
AUD_SDA: U1.10 (PF0); also elsewhere on the board
AUD_WCLK: U1.3 (PE4); also elsewhere on the board
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
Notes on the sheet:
VOICEVAULT C1 | STANDALONE SECURE AUDIO ENDPOINT | CIRCUIT REVIEW
NOT FOR FABRICATION. Hierarchical circuits under review; all PCB routing remains incomplete.
STDC14 pin 3 is target voltage sense, NOT a power input.
Use an external STLINK-V3MINIE. Target supply is separate.
Pins 13/14 use TARGET RX/TX naming. UART6 on PC8/PC9.
Power, radio, secure elements, controls and offline-update interfaces: see child sheets.
Main debug and radio debug are separate; probes measure target voltage only.
Display/touch: see child sheets. Rev C removes Qi, NFC and vibration.
Audio codec, CTIA headset, physical microphone disconnect and microSD are additions.
Prototype has open debug access and public diagnostic material. Physical security remains unqualified.
MCU: STM32U5G9ZJT6Q. Safe 7-derived platform; prototype package and provisional 70 x 45 mm outline need qualification.

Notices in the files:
hardware/rev-b/README.md:
Sources and licensing:
[Source manifest](reference/source-manifest.json), pinned ST ball data, manufacturer-source hashes and [library notices](LIBRARY_NOTICE.md) accompany the design. The new hardware adaptation uses [CERN-OHL-S-2.0](LICENSE); upstream and component-library notices retain their own terms. VoiceVault is independent and has no Trezor endorsement.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
